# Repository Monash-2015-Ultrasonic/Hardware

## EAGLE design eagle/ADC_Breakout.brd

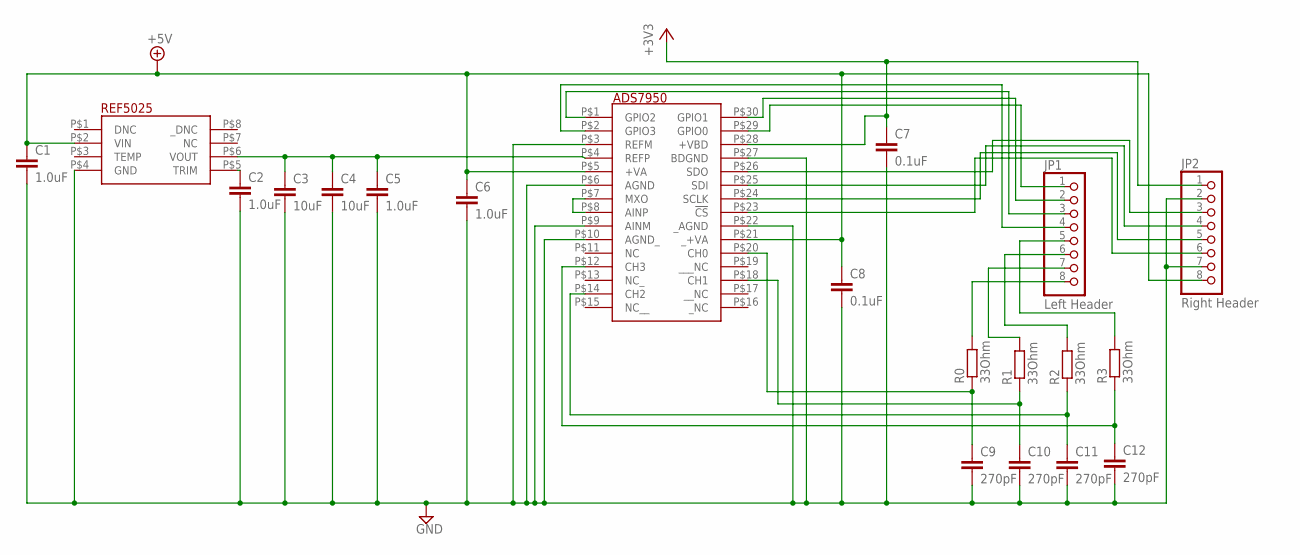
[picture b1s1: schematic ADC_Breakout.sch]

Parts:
ADS7950: ADS7950; TSSOP-30
C1, C2, C5, C6: 1.0uF; C0603
C3, C4: 10uF; C0805
C7, C8: 0.1uF; C0603
C9, C10, C11, C12: 270pF; C0603
JP1: Left Header; 1X08
JP2: Right Header; 1X08
R0, R1, R2, R3: 33Ohm; R1206
REF5025: REF5025; SOIC-8

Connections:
+3V3: ADS7950.P$28 (+VBD), C7.1, JP2.1
+5V: ADS7950.P$5 (+VA), ADS7950.P$21 (_+VA), C1.1, C6.1, C8.1, JP2.8, REF5025.P$2 (VIN)
GND: ADS7950.P$3 (REFM), ADS7950.P$6 (AGND), ADS7950.P$9 (AINM), ADS7950.P$10 (AGND_), ADS7950.P$22 (_AGND), ADS7950.P$27 (BDGND), C1.2, C2.2, C3.2, C4.2, C5.2, C6.2, C7.2, C8.2, C9.2, C10.2, C11.2, C12.2, JP2.2, JP2.7, REF5025.P$4 (GND)
unnamed: C2.1, REF5025.P$5 (TRIM)
unnamed: ADS7950.P$29 (GPIO0), JP1.1
unnamed: ADS7950.P$7 (MXO), ADS7950.P$8 (AINP)
unnamed: ADS7950.P$30 (GPIO1), JP1.2
unnamed: ADS7950.P$1 (GPIO2), JP1.3
unnamed: ADS7950.P$2 (GPIO3), JP1.4
unnamed: JP1.7, R1.2
unnamed: JP1.6, R2.2
unnamed: JP1.5, R3.2
unnamed: ADS7950.P$18 (CH1), C10.1, R1.1
unnamed: ADS7950.P$14 (CH2), C11.1, R2.1
unnamed: JP1.8, R0.2
unnamed: ADS7950.P$23 (!CS!), JP2.6
unnamed: ADS7950.P$12 (CH3), C12.1, R3.1
unnamed: ADS7950.P$26 (SDO), JP2.3
unnamed: ADS7950.P$25 (SDI), JP2.4
unnamed: ADS7950.P$24 (SCLK), JP2.5
unnamed: ADS7950.P$20 (CH0), C9.1, R0.1
REFP: ADS7950.P$4 (REFP), C3.1, C4.1, C5.1, REF5025.P$6 (VOUT)

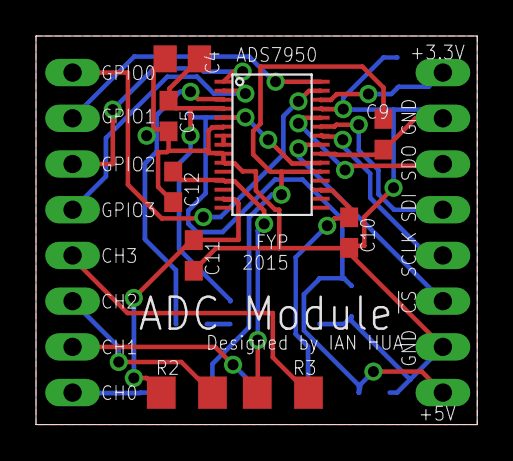
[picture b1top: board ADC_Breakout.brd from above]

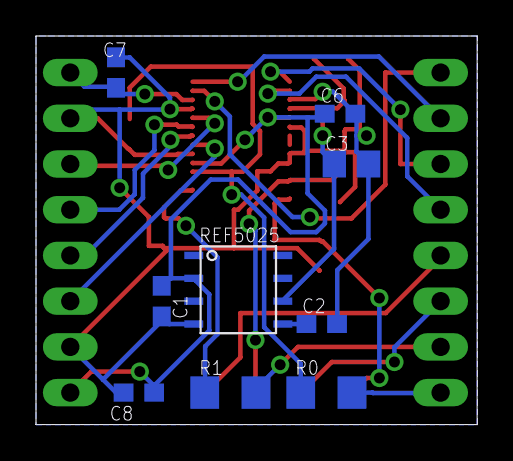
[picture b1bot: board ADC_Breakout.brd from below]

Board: 2 copper layers, 24.5 x 21.6 mm, 20 parts (9 on the bottom side), 22 nets.

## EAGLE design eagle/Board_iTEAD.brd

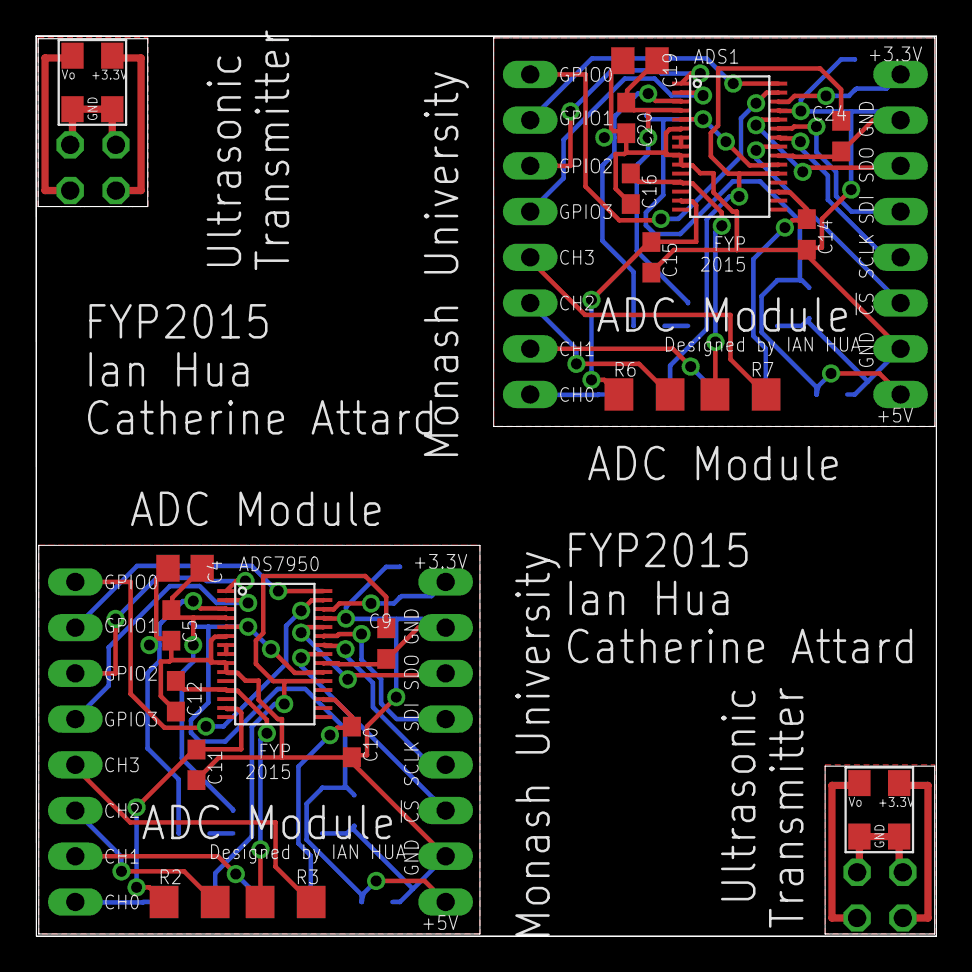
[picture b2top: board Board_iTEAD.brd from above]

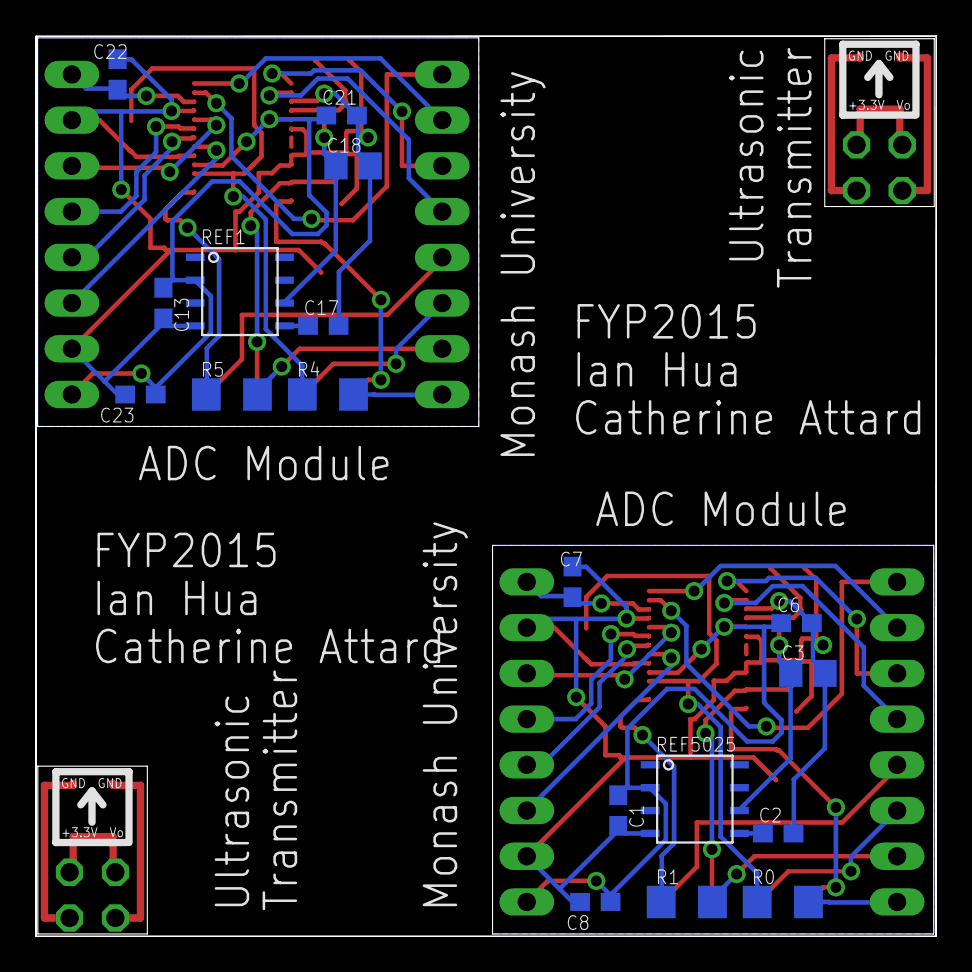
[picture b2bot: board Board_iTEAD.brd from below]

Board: 2 copper layers, 50.0 x 50.0 mm, 44 parts (18 on the bottom side), 50 nets.

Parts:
ADS1, ADS7950: ADS7950; TSSOP-30
C1, C2, C5, C6, C13, C17, C20, C21: 1.0uF; C0603
C3, C4, C18, C19: 10uF; C0805
C7, C8, C22, C23: 0.1uF; C0603
C9, C10, C11, C12, C14, C15, C16, C24: 270pF; C0603
JP1, JP3: Left Header; 1X08
JP2, JP4: Right Header; 1X08
JP5, JP6: 2X02
R0, R1, R2, R3, R4, R5, R6, R7: 33Ohm; R1206
REF1, REF5025: REF5025; SOIC-8
SPM0404UD1, SPM0404UD5: SPM0404UD5; KNOWLES_SPM

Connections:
+3V1: ADS1.P$28, C22.1, JP4.1
+3V2: JP5.1, SPM0404UD5.P$4
+3V3: ADS7950.P$28, C7.1, JP2.1
+3V4: JP6.1, SPM0404UD1.P$4
+5V: ADS7950.P$5, ADS7950.P$21, C1.1, C6.1, C8.1, JP2.8, REF5025.P$2
+5V1: ADS1.P$5, ADS1.P$21, C13.1, C21.1, C23.1, JP4.8, REF1.P$2
GND: ADS7950.P$3, ADS7950.P$6, ADS7950.P$9, ADS7950.P$10, ADS7950.P$22, ADS7950.P$27, C1.2, C2.2, C3.2, C4.2, C5.2, C6.2, C7.2, C8.2, C9.2, C10.2, C11.2, C12.2, JP2.2, JP2.7, REF5025.P$4
GND1: ADS1.P$3, ADS1.P$6, ADS1.P$9, ADS1.P$10, ADS1.P$22, ADS1.P$27, C13.2, C14.2, C15.2, C16.2, C17.2, C18.2, C19.2, C20.2, C21.2, C22.2, C23.2, C24.2, JP4.2, JP4.7, REF1.P$4
GND2: JP5.3, JP5.4, SPM0404UD5.P$2, SPM0404UD5.P$3
GND3: JP6.3, JP6.4, SPM0404UD1.P$2, SPM0404UD1.P$3
unnamed: C2.1, REF5025.P$5
unnamed: C17.1, REF1.P$5
unnamed: ADS7950.P$29, JP1.1
unnamed: ADS7950.P$7, ADS7950.P$8
unnamed: ADS7950.P$30, JP1.2
unnamed: ADS7950.P$1, JP1.3
unnamed: ADS7950.P$2, JP1.4
unnamed: ADS1.P$29, JP3.1
unnamed: JP1.7, R1.2
unnamed: JP1.6, R2.2
unnamed: JP1.5, R3.2
unnamed: ADS1.P$30, JP3.2
unnamed: ADS7950.P$18, C10.1, R1.1
unnamed: ADS7950.P$14, C11.1, R2.1
unnamed: JP1.8, R0.2
unnamed: ADS7950.P$23, JP2.6
unnamed: ADS7950.P$12, C12.1, R3.1
unnamed: ADS7950.P$26, JP2.3
unnamed: ADS7950.P$25, JP2.4
unnamed: ADS7950.P$24, JP2.5
unnamed: ADS7950.P$20, C9.1, R0.1
unnamed: ADS1.P$1, JP3.3
unnamed: ADS1.P$2, JP3.4
unnamed: JP3.8, R4.2
unnamed: JP3.7, R5.2
unnamed: JP3.6, R6.2
unnamed: JP3.5, R7.2
unnamed: ADS1.P$18, C14.1, R5.1
unnamed: ADS1.P$14, C15.1, R6.1
unnamed: ADS1.P$12, C16.1, R7.1
unnamed: ADS1.P$26, JP4.3
unnamed: ADS1.P$25, JP4.4
unnamed: ADS1.P$24, JP4.5
unnamed: ADS1.P$23, JP4.6
unnamed: ADS1.P$20, C24.1, R4.1
unnamed: ADS1.P$7, ADS1.P$8
unnamed: JP5.2, SPM0404UD5.P$1
unnamed: JP6.2, SPM0404UD1.P$1
REFP: ADS7950.P$4, C3.1, C4.1, C5.1, REF5025.P$6
REFP1: ADS1.P$4, C18.1, C19.1, C20.1, REF1.P$6

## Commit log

2015-03-25 Added schematic for ADC Module
    Needs Mic and MXO test point
2015-03-26 Full ADC Module and Mic Module
2015-03-26 Added screenshots
2015-03-26 GERBERS GENERATED for COMPLETE ITEAD SUBMISSION
2015-03-26 Completed PCB
2015-03-26 Gerber V2 - using iTEAD CAM settings
2015-03-27 Tidied
2015-04-23 Added pinout diagrams
